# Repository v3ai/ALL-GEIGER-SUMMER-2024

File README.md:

## These files contain all the work Rhett Applestone has done in the summer of 2024 for the MIT-NSE Geiger Project

NOTICE:

REV-10 is the newest most stable board, make sure all solder joints are secure.

We use Kicad for PCB design, and Freecad primarily for 3d modeling and engineering drawings. Although now, Ondsel (a Freecad derivitive)
seem much easier to use an more polished and uses the same file format as freecad.(FCStd) 

I choose to switch to Kicad so anyone could build upon the work I did. Kicad Is Free and open source. Fusion-360 Cad and Electronis is "free" for students and maybe hobbyists, but anyone who has dealt with
software knows there's a big difference between a link to download software immedately and like a "fill out this form and make an account, request a trial and yada yada."

Fusion-360 is also heavily cloud based and really doesnt like you to save things to disk. Cloud based in my opinion is garbage, I don't want to be forever locked in to thier ecosystem, I want to save files to my disk.

Fusion-360 is also just pretty bad software in my opinion. Dont get my wrong it's ok, but like, I want my software to be good for life, load fast, and never ask me to sign in or connect to wifi, or say I need to update etc.

Fusion also loads really slow, which is infuriating when you want to make small changes. Kicad loads in less than 1 second on my computer. 

Both Kicad and Freecad (Or Ondsel) do things somewhat differently from other EDA or CAD programs, and I would recomend watching and completing a tutorial on both

There is another Experimental board in the EXPERIMENTAL-BOARD folder, seems to have some problems with mosfets heating up, more investigation needed.

### Getting Software set up

For linux (mint)

Run thiese commands in the terminal

### Installing Kicad

```
sudo add-apt-repository ppa:kicad/kicad-8.0-releases
sudo apt update
sudo apt install kicad
```

### Installing Freecad

```
#This line not necessary if you're on ubuntu
sudo rm /etc/apt/preferences.d/nosnap.pref

sudo apt install snapd -y

sudo snap install --edge freecad

snap refresh
```

### Installing Ondsel		

go to their github and download correct release https://github.com/Ondsel-Development/FreeCAD/releases

or

https://ondsel.com/

go to their website and make an account then download, 

appimages have to be made executable and then can be run

### Mac, Windows, other linux

Go to Kicad and Freecad (or Ondsel)'s websites and see download instructions

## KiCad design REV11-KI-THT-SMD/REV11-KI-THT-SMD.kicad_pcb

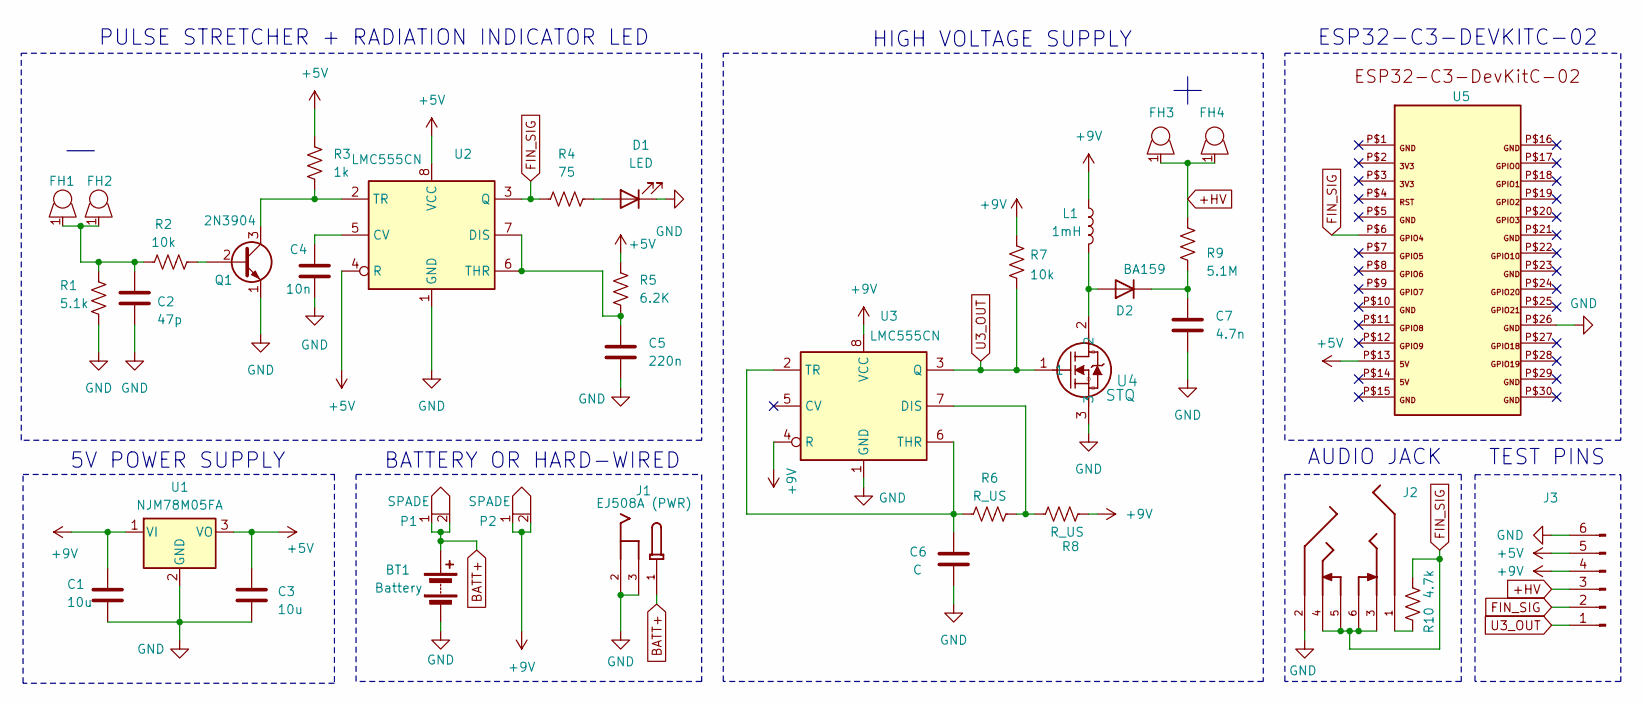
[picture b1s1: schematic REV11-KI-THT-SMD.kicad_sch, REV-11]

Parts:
BT1: Battery; BatteryHolder_MPD_BA9VPC_1xPP3
C1, C3: 10u; C_THT_SMD
C2: 47p; C_THT_SMD
C4: 10n; C_THT_SMD
C5: 220n; C_THT_SMD
C6: C; C_THT_SMD
C7: 4.7n; CHV
D1: LED; LED_D3.0mm
D2: BA159; D_DO-41_SOD81_P7.62mm_Horizontal
FH1, FH2, FH3, FH4: 36-3530-ND
J1: EJ508A (PWR); MPD_EJ508A; PARTREV J
J2: 54-00298; PARTREV A
J3: PinHeader_1x06_P2.54mm_Vertical
L1: 1mH; L_Radial_D8.7mm_P5.00mm_Fastron_07HCP
P1, P2: SPADE; 0197084013
Q1: 2N3904; TO-92_Inline_Wide
R1: 5.1k; R_BIG
R2, R7: 10k; R_SMALL
R3: 1k; R_SMALL
R4: 75; R_SMALL
R5: 6.2K; R_SMALL
R6, R8: R_US; R_SMALL
R9: 5.1M; R_SMALL
R10: 4.7k; R_SMALL
U1: NJM78M05FA; TO-220-3_Vertical
U2, U3: LMC555CN; DIP-8_W7.62mm
U4: STQ; TO-92_Inline_Wide
U5: ESP32-C3-DEVKITC-02HOLES; ESP32-C3-DevKitC-02

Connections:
+5V: C3.1, J3.5, R3.1, R5.1, U1.3 (VO), U2.4 (R), U2.8 (VCC), U5.P$13
+9V: C1.1, J3.4, L1.1, P2.1, P2.2, R7.1, R8.1, U1.1 (VI), U3.4 (R), U3.8 (VCC)
+HV: FH3.1, FH4.1, J3.3, R9.2
BATT+: BT1.1 (+), J1.1, P1.1, P1.2
FIN_SIG: J2.3, J2.4, J2.5, J2.6, J3.2, R4.1, R10.2, U2.3 (Q), U5.P$6
GND: BT1.2 (-), C1.2, C2.2, C3.2, C4.1, C5.2, C6.2, C7.2, D1.1 (K), J1.2, J1.3, J2.2, J3.6, Q1.1 (E), R1.2, U1.2 (GND), U2.1 (GND), U3.1 (GND), U4.3, U5.P$26
unnamed: C2.1, FH1.1, FH2.1, R1.1, R2.1
unnamed: D1.2 (A), R4.2
unnamed: D2.2 (A), L1.2, U4.2
unnamed: C7.1, D2.1 (K), R9.1
unnamed: J2.1, R10.1
unnamed: Q1.2 (B), R2.2
unnamed: Q1.3 (C), R3.2, U2.2 (TR)
unnamed: C4.2, U2.5 (CV)
unnamed: C5.1, R5.2, U2.6 (THR), U2.7 (DIS)
unnamed: R6.1, R8.2, U3.7 (DIS)
unnamed: C6.1, R6.2, U3.2 (TR), U3.6 (THR)
U3_OUT: J3.1, R7.2, U3.3 (Q), U4.1

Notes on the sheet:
HIGH VOLTAGE SUPPLY
AUDIO JACK
TEST PINS
BATTERY OR HARD-WIRED
ESP32-C3-DEVKITC-02
PULSE STRETCHER + RADIATION INDICATOR LED
5V POWER SUPPLY

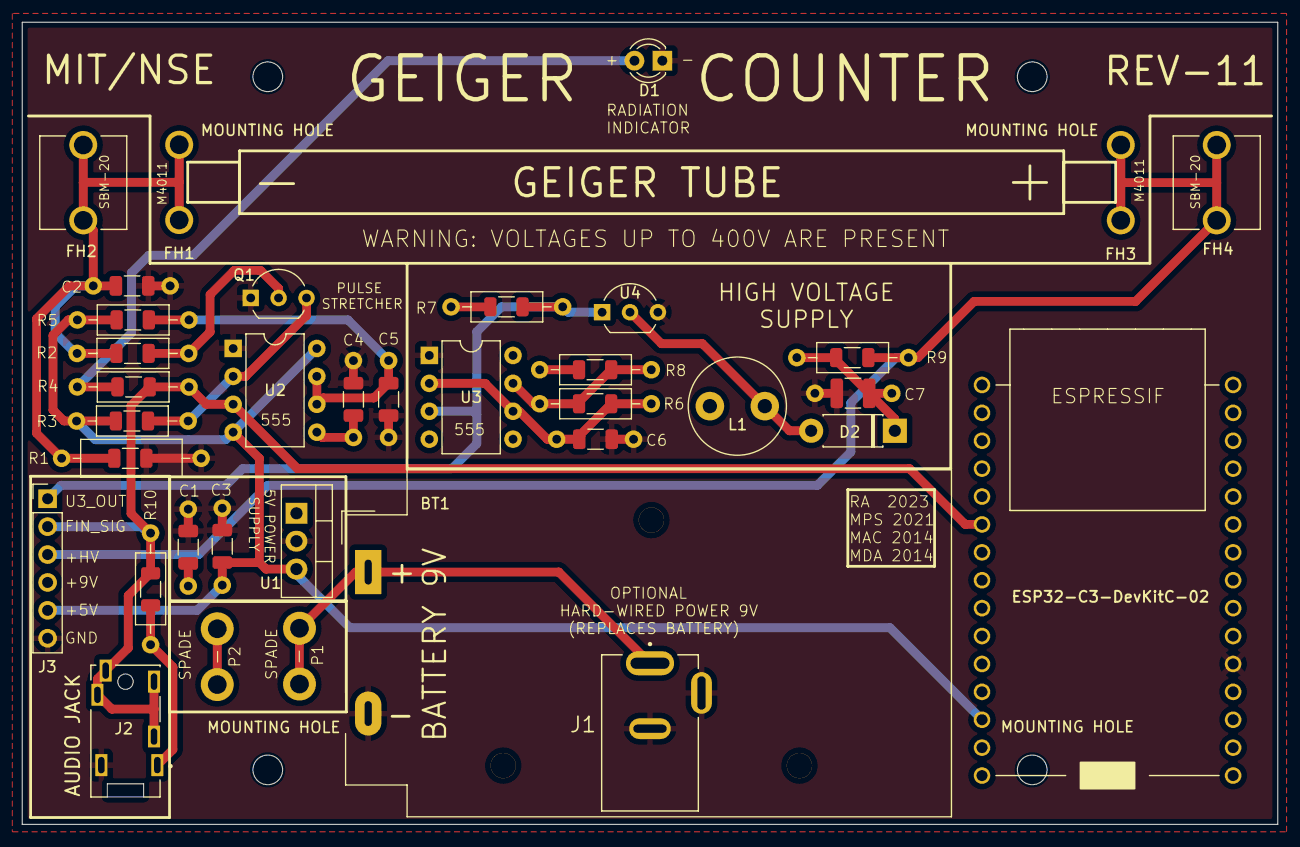
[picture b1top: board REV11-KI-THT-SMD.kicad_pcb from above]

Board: 2 copper layers, 114.3 x 73.0 mm, 40 parts (0 on the bottom side), 18 nets.

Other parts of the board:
MOUNTING HOLE: MountingHole_2.7mm
MOUNTING HOLE#2, MOUNTING HOLE#3, MOUNTING HOLE#4: MountingHole_2.7mm

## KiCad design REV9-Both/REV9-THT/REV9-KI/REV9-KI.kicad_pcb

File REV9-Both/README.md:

There were two Rev9s, the first one (SMD) was made with fusion-360, and another with kicad

I choose to switch to kicad so anyone could build upon the work I did. Kicad Is Free and open source. Fusion-360 is "free" for students , but anyone who has dealt with

software knows there's a bit difference between a link to download immedately and like a "fill out this form and make an account and yada yada."

Fusion-360 is also cloud based and really doesnt like you to save things to disk. Cloud based in my opinion is garbage, and It's an element of control.

Fusion-360 is also just pretty bad software in my opinion. Dont get my wrong it's ok, but like, I want my software to be good for life, and never ask me to sign in or connect to wifi, or say I need to update etc.

Fusion also loads really slow, which is infuriating when you want to make small changes. Kicad loads in less than 1 second on my computer.

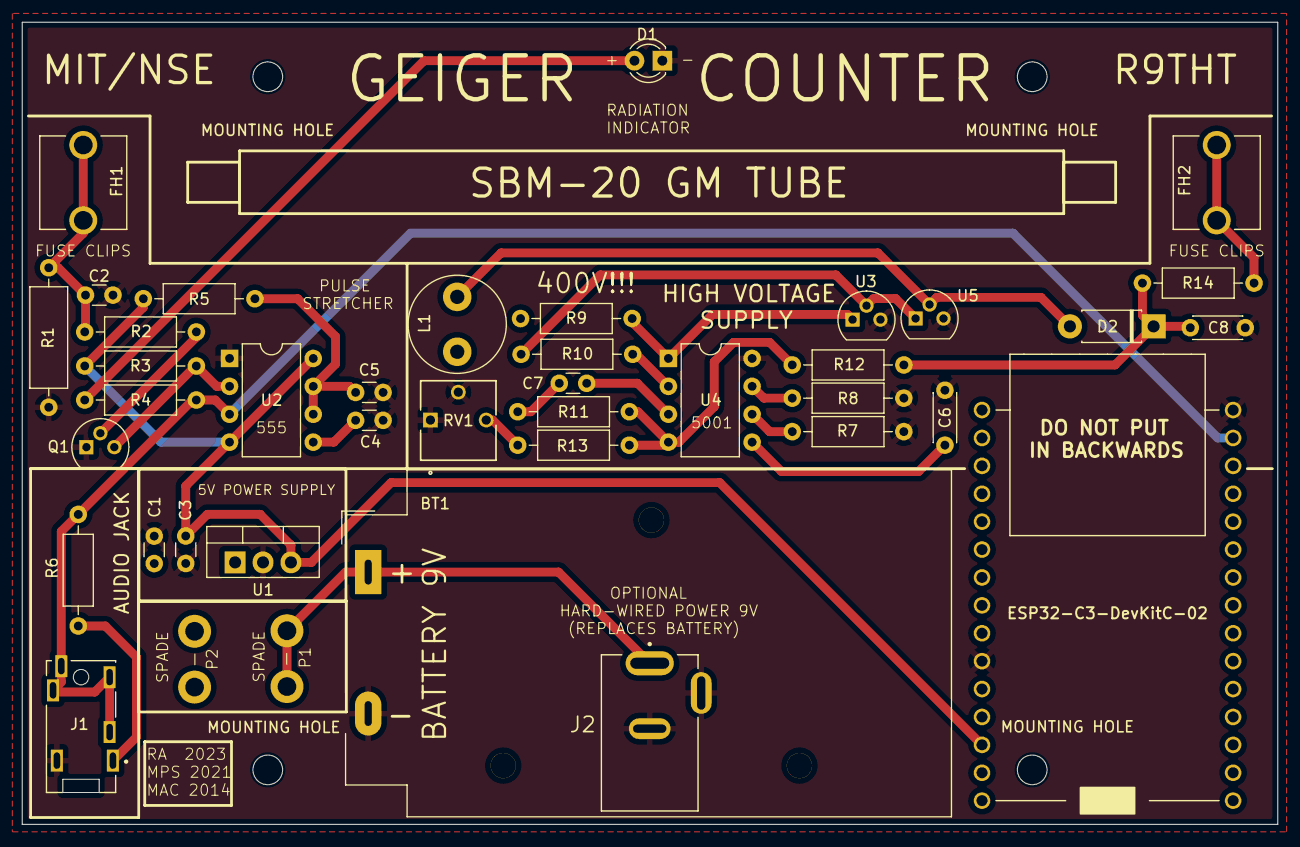
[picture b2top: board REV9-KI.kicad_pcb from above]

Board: 2 copper layers, 114.3 x 73.0 mm, 44 parts (0 on the bottom side), 24 nets.

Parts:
BT1: Battery; BatteryHolder_MPD_BA9VPC_1xPP3
C1, C3: 10u; C_Disc_D3.0mm_W1.6mm_P2.50mm
C2: 47p; C_Disc_D3.0mm_W1.6mm_P2.50mm
C4, C7: 10n; C_Disc_D3.0mm_W1.6mm_P2.50mm
C5: 220n; C_Disc_D3.0mm_W1.6mm_P2.50mm
C6: 1u; C_Disc_D4.3mm_W1.9mm_P5.00mm
C8: 4.7n; C_Disc_D4.3mm_W1.9mm_P5.00mm
D1: LED; LED_D3.0mm
D2: BA159; D_DO-41_SOD81_P7.62mm_Horizontal
FH1, FH2: 36-3530-ND
J1: 54-00298
J2: EJ508A (PWR); MPD_EJ508A
L1: 1mH; L_Radial_D8.7mm_P5.00mm_Fastron_07HCP
MOUNTING HOLE: MountingHole_2.7mm
MOUNTING HOLE#2, MOUNTING HOLE#3, MOUNTING HOLE#4: MountingHole_2.7mm
P1, P2: SPADE; 0197084013
Q1: 2N3904; TO-92
R1: 5.1k; R_Axial_DIN0309_L9.0mm_D3.2mm_P12.70mm_Horizontal
R2, R9, R10: 10k; R_Axial_DIN0207_L6.3mm_D2.5mm_P10.16mm_Horizontal
R3: 1k; R_Axial_DIN0207_L6.3mm_D2.5mm_P10.16mm_Horizontal
R4: 75; R_Axial_DIN0207_L6.3mm_D2.5mm_P10.16mm_Horizontal
R5: 6.2K; R_Axial_DIN0207_L6.3mm_D2.5mm_P10.16mm_Horizontal
R6, R11: 4.7k; R_Axial_DIN0207_L6.3mm_D2.5mm_P10.16mm_Horizontal
R7: 4.7M; R_Axial_DIN0207_L6.3mm_D2.5mm_P10.16mm_Horizontal
R8: 6.8M; R_Axial_DIN0207_L6.3mm_D2.5mm_P10.16mm_Horizontal
R12: 10M; R_Axial_DIN0207_L6.3mm_D2.5mm_P10.16mm_Horizontal
R13: 22k; R_Axial_DIN0207_L6.3mm_D2.5mm_P10.16mm_Horizontal
R14: 5.1M; R_Axial_DIN0207_L6.3mm_D2.5mm_P10.16mm_Horizontal
RV1: R_Potentiometer_US 20k; POT_3362P
U1: NJM78M05FA; TO-220-3_Vertical
U2: LMC555CN; DIP-8_W7.62mm
U3, U5: STQ1HNK60R-AP; TO-92
U4: TL5001AIP; DIP-8_W7.62mm
U6: ESP32-C3-DEVKITC-02HOLES; ESP32-C3-DevKitC-02

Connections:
5001_OUT: R9.2, U3.1, U4.1 (V_{O})
+5V: C3.1, R3.1, R5.1, U1.3 (VO), U2.4 (R), U2.8 (VCC), U6.P$13
+9V: C1.1, L1.1, P2.1, P2.2, R9.1, R10.1, U1.1 (VI), U4.2 (V_{CC})
BATT+: BT1.1 (+), J2.1, P1.1, P1.2
FINAL_SIGNAL: J1.3, J1.4, J1.5, J1.6, R4.1, R6.2, U2.3 (Q), U6.P$17
GND: BT1.2 (-), C1.2, C2.2, C3.2, C4.1, C5.2, C6.1, C8.2, D1.1 (K), J1.2, J2.2, J2.3, Q1.1 (E), R1.2, R7.1, R8.1, RV1.1, RV1.2, U1.2 (GND), U2.1 (GND), U3.3, U4.8 (GND), U5.3, U6.P$10, U6.P$16
unnamed: C2.1, FH1.1, R1.1, R2.1
unnamed: C7.2, R11.1
unnamed: D1.2 (A), R4.2
unnamed: D2.2 (A), L1.2, U5.2
unnamed: C8.1, D2.1 (K), R12.2, R14.1
unnamed: FH2.1, R14.2
unnamed: J1.1, R6.1
unnamed: Q1.2 (B), R2.2
unnamed: Q1.3 (C), R3.2, U2.2 (TR)
unnamed: R10.2, U3.2, U5.1
unnamed: R13.2, RV1.3
unnamed: C4.2, U2.5 (CV)
unnamed: C5.1, R5.2, U2.6 (THR), U2.7 (DIS)
unnamed: C7.1, U4.3 (COMP)
unnamed: R7.2, U4.6 (DTC)
unnamed: R11.2, R12.1, R13.1, U4.4 (FB)
unnamed: R8.2, U4.7 (RT)
unnamed: C6.2, U4.5 (SCP)

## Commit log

2024-08-02 init
2024-08-02 added REV11
2024-08-02 removed backups
2024-08-05 new files, readme, etc
2024-08-05 added instructions for end
2024-08-05 added r9s
2024-08-06 august 6
2024-08-06 updated insert things
2024-08-07 edited docs
2024-08-08 working on documentation
2024-08-08 adding documentation
2024-08-08 adding pic
2024-08-15 added pics, added new manual
2024-08-15 august 15th
2024-08-15 added todos
2025-01-05 qcom
